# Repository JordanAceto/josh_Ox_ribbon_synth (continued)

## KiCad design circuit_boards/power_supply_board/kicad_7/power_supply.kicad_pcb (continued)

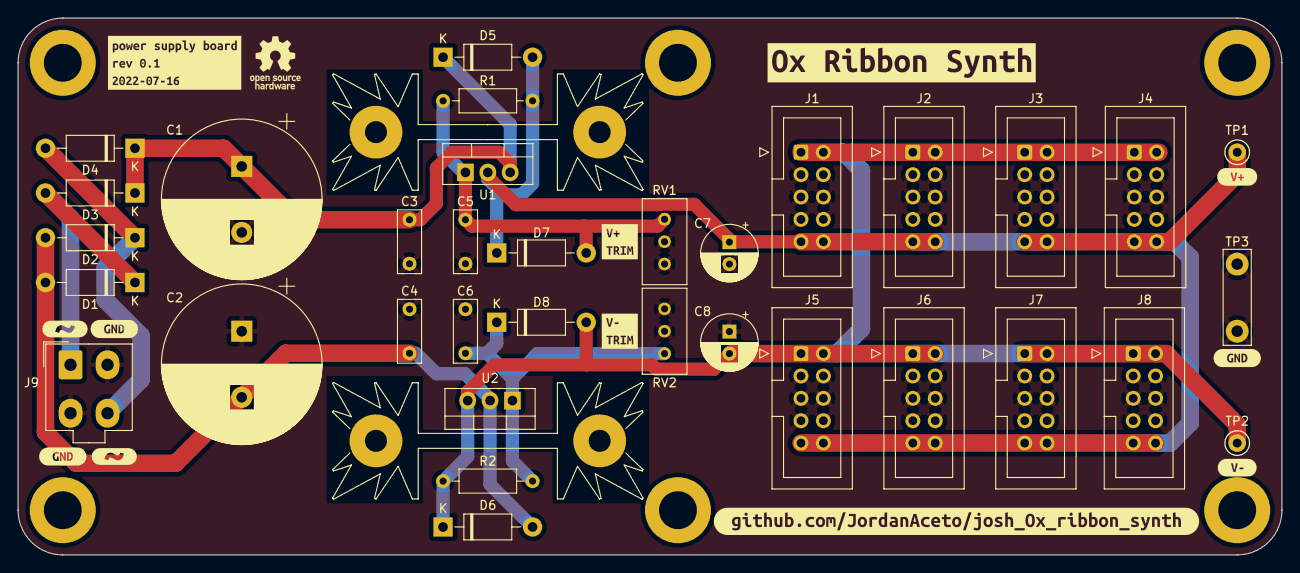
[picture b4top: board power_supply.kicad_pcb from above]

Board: 2 copper layers, 143.5 x 61.0 mm, 46 parts (0 on the bottom side), 9 nets.

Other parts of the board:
kibuzzard-62AC7A9F: G***; kibuzzard-62AC7A9F
kibuzzard-62B8A02A, kibuzzard-62B8A02A#2: G***; kibuzzard-62B8A02A
kibuzzard-62B8A297: G***; kibuzzard-62B8A297
kibuzzard-62B89F9F: G***; kibuzzard-62B89F9F
kibuzzard-62B89F93, kibuzzard-62B89F93#2, kibuzzard-62B89F93#3: G***; kibuzzard-62B89F93
kibuzzard-62B89FA9: G***; kibuzzard-62B89FA9
kibuzzard-62B89FC4: G***; kibuzzard-62B89FC4
kibuzzard-62B89FD2: G***; kibuzzard-62B89FD2
kibuzzard-62D2BBF1: G***; kibuzzard-62D2BBF1

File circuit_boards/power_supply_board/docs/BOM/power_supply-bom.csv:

Row,Description,Part,References,Value,Footprint,Quantity Per PCB,Status,Datasheet
1,Unpolarized capacitor,C,C3 C4 C5 C6,100n,C_Rect_L7.0mm_W2.5mm_P5.00mm,4, ,~
2,Polarized capacitor,C_Polarized,C7 C8,10u,CP_Radial_D6.3mm_P2.50mm,2, ,~
3,Polarized capacitor,C_Polarized,C1 C2,3300u,CP_Radial_D18.0mm_P7.50mm,2, ,~
4,"100V 1A General Purpose Rectifier Diode, DO-41",1N4002,D1 D2 D3 D4 D5 D6 D7 D8,1N4002,D_DO-41_SOD81_P10.16mm_Horizontal,8, ,http://www.vishay.com/docs/88503/1n4001.pdf
5,"Generic connector, single row, 01x04, script generated (kicad-library-utils/schlib/autogen/connector/)",Conn_01x04,J9,AC_power_in,Molex_Mini-Fit_Jr_5566-04A_2x02_P4.20mm_Vertical,1, ,~
6,"Generic connector, double row, 02x05, odd/even pin numbering scheme (row 1 odd numbers, row 2 even numbers), script generated (kicad-library-utils/schlib/autogen/connector/)",Conn_02x05_Odd_Even,J1 J2 J3 J4 J5 J6 J7 J8,power_out,IDC-Header_2x05_P2.54mm_Vertical,8, ,~
7,Resistor,R,R1 R2,240,R_Axial_DIN0207_L6.3mm_D2.5mm_P10.16mm_Horizontal,2, ,~
8,Trim-potentiometer,R_Potentiometer_Trim,RV1 RV2,5k,Potentiometer_Bourns_3296W_Vertical,2, ,~
9,"1.5A 35V Adjustable Linear Regulator, TO-220",LM317_TO-220,U1,LM317_TO-220,TO-220-3_Vertical,1, ,http://www.ti.com/lit/ds/symlink/lm317.pdf
10,"Negative 1.5A 35V Adjustable Linear Regulator, TO-220",LM337_TO220,U2,LM337_TO220,TO-220-3_Vertical,1, ,http://www.ti.com/lit/ds/symlink/lm337-n.pdf





Project info:
Schematic:,power_supply
Variant:,default
Revision:,0
Date:,2022-06-26
KiCad Version:,6.0.5+dfsg-1~bpo11+1
Statistics:
Component Groups:,10
Component Count:,31 (0 SMD/ 31 THT)
Fitted Components:,31 (0 SMD/ 31 THT)
Number of PCBs:,1
Total Components:,31

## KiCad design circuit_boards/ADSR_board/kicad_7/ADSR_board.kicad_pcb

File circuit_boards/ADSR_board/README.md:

# Triple ADSR Board

## [SCHEMATIC](https://github.com/JordanAceto/josh_Ox_ribbon_synth/blob/master/circuit_boards/ADSR_board/docs/ADSR_board_schematic.pdf)

Three ADSR envelope generators with short and long time range switch.

A comparator and analog switch ensure that the sustain control reacts quickly during sustain phases, even when the decay control is set for long time constants.

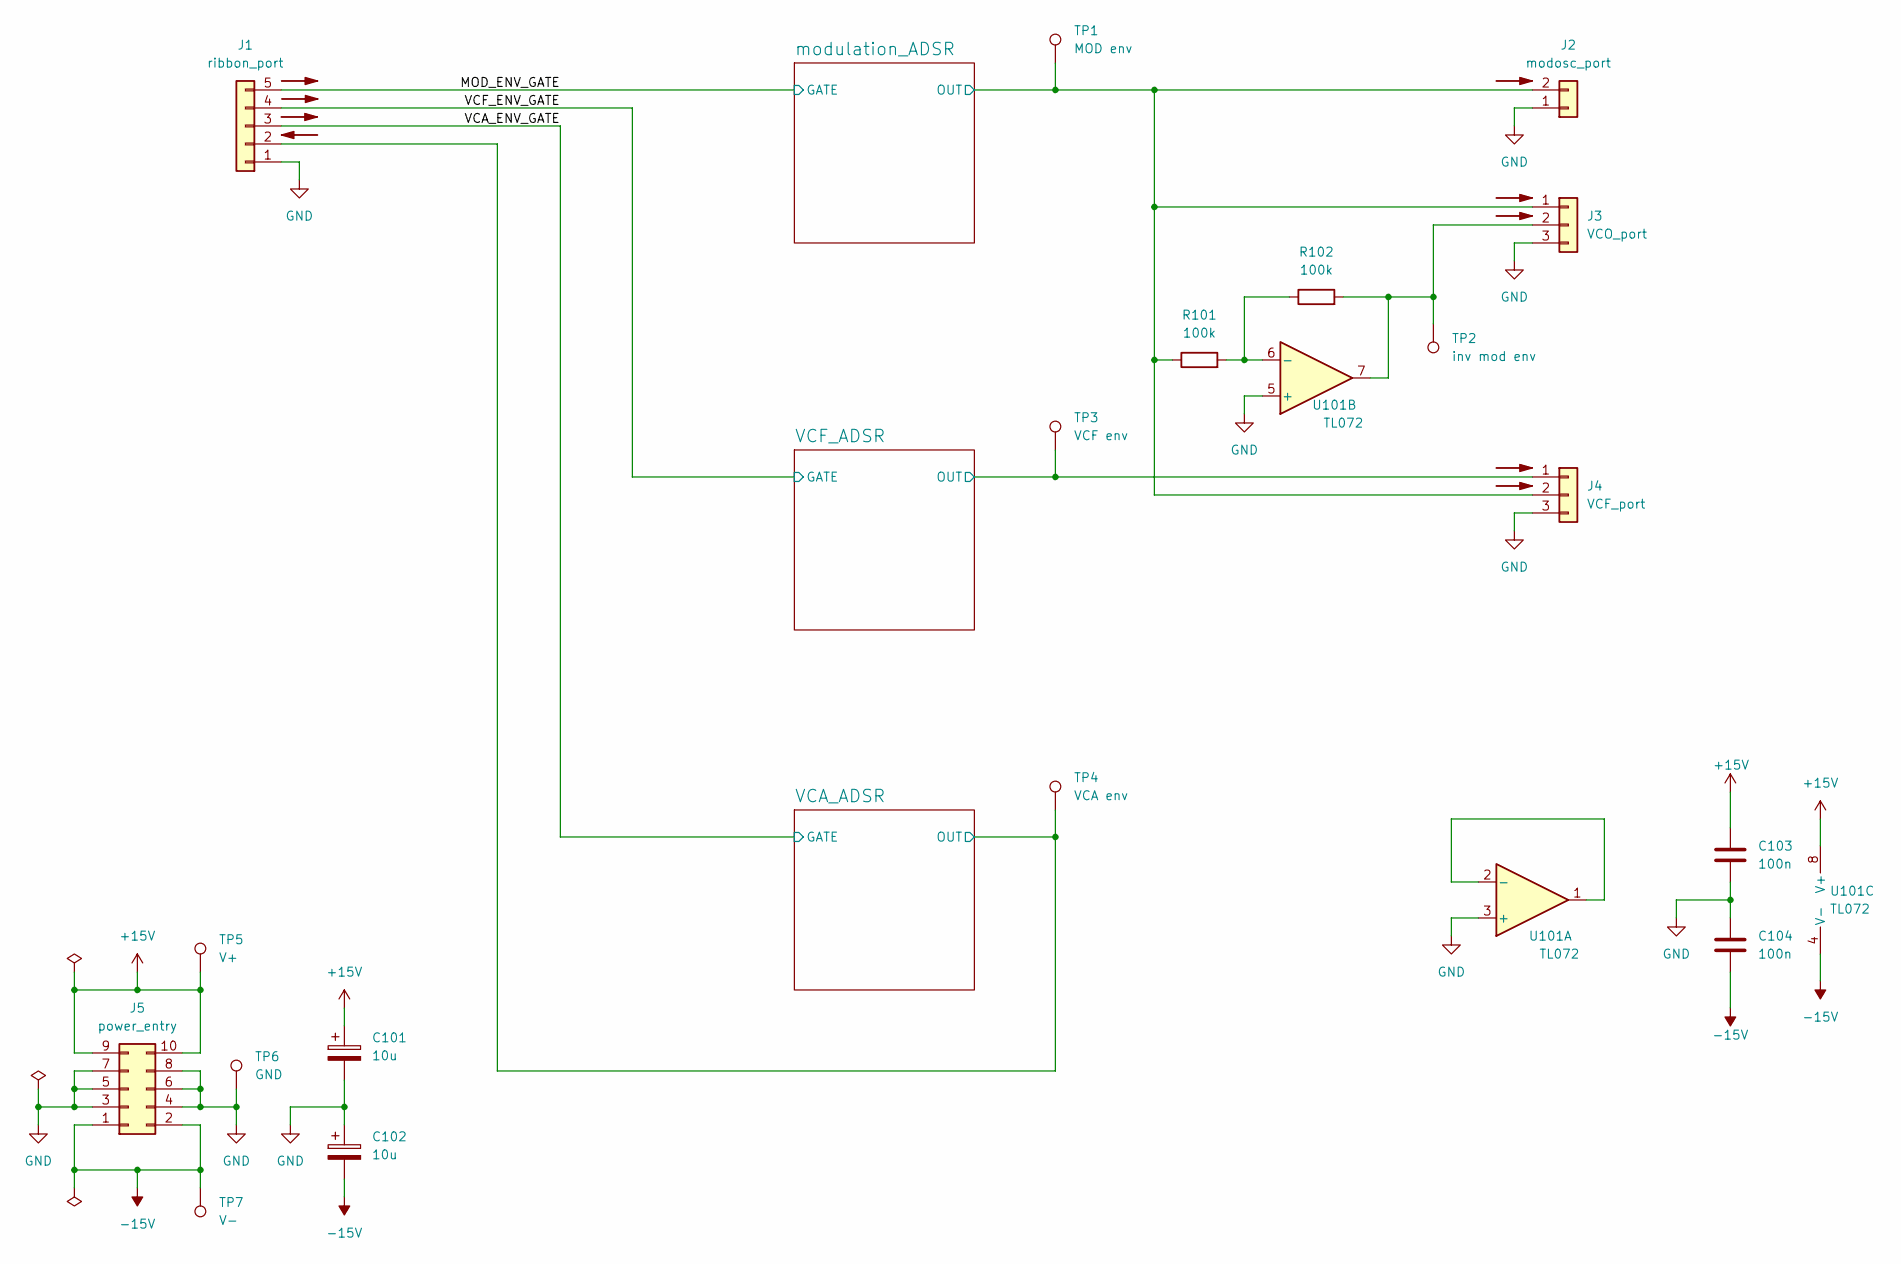
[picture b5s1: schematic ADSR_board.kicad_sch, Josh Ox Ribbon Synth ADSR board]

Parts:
C101, C102: 10u; CP_Radial_D6.3mm_P2.50mm
C103, C104: 100n; C_0805_2012Metric
J1: ribbon_port; Molex_KK-254_AE-6410-05A_1x05_P2.54mm_Vertical
J2: modosc_port; Molex_KK-254_AE-6410-02A_1x02_P2.54mm_Vertical
J3: VCO_port; Molex_KK-254_AE-6410-03A_1x03_P2.54mm_Vertical
J4: VCF_port; Molex_KK-254_AE-6410-03A_1x03_P2.54mm_Vertical
J5: power_entry; IDC-Header_2x05_P2.54mm_Vertical
R101, R102: 100k; R_0805_2012Metric
TP1: MOD env; TestPoint_Keystone_5000-5004_Miniature
TP2: inv mod env; TestPoint_Keystone_5000-5004_Miniature
TP3: VCF env; TestPoint_Keystone_5000-5004_Miniature
TP4: VCA env; TestPoint_Keystone_5000-5004_Miniature
TP5: V+; TestPoint_Keystone_5000-5004_Miniature
TP6: GND; TestPoint_Bridge_Pitch7.62mm_Drill1.3mm
TP7: V-; TestPoint_Keystone_5000-5004_Miniature
U101: TL072; SOIC-8_3.9x4.9mm_P1.27mm

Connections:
+15V: C101.1, C103.1, J5.9, J5.10, TP5.1, U101.8 (V+); also elsewhere on the board
-15V: C102.2, C104.2, J5.1, J5.2, TP7.1, U101.4 (V-); also elsewhere on the board
/MOD_ENV_GATE: J1.5; also elsewhere on the board
/VCA_ADSR/OUT: J1.2, TP4.1; also elsewhere on the board
/VCA_ENV_GATE: J1.3; also elsewhere on the board
/VCF_ADSR/OUT: J4.1, TP3.1; also elsewhere on the board
/VCF_ENV_GATE: J1.4; also elsewhere on the board
/modulation_ADSR/OUT: J2.2, J3.1, J4.2, R101.1, TP1.1; also elsewhere on the board
GND: C101.2, C102.1, C103.2, C104.1, J1.1, J2.1, J3.3, J4.3, J5.3, J5.4, J5.5, J5.6, J5.7, J5.8, TP6.1, U101.3 (+), U101.5 (+); also elsewhere on the board
unnamed: J3.2, R102.2, TP2.1, U101.7
unnamed: R101.2, R102.1, U101.6 (-)
unnamed: U101.1, U101.2 (-)

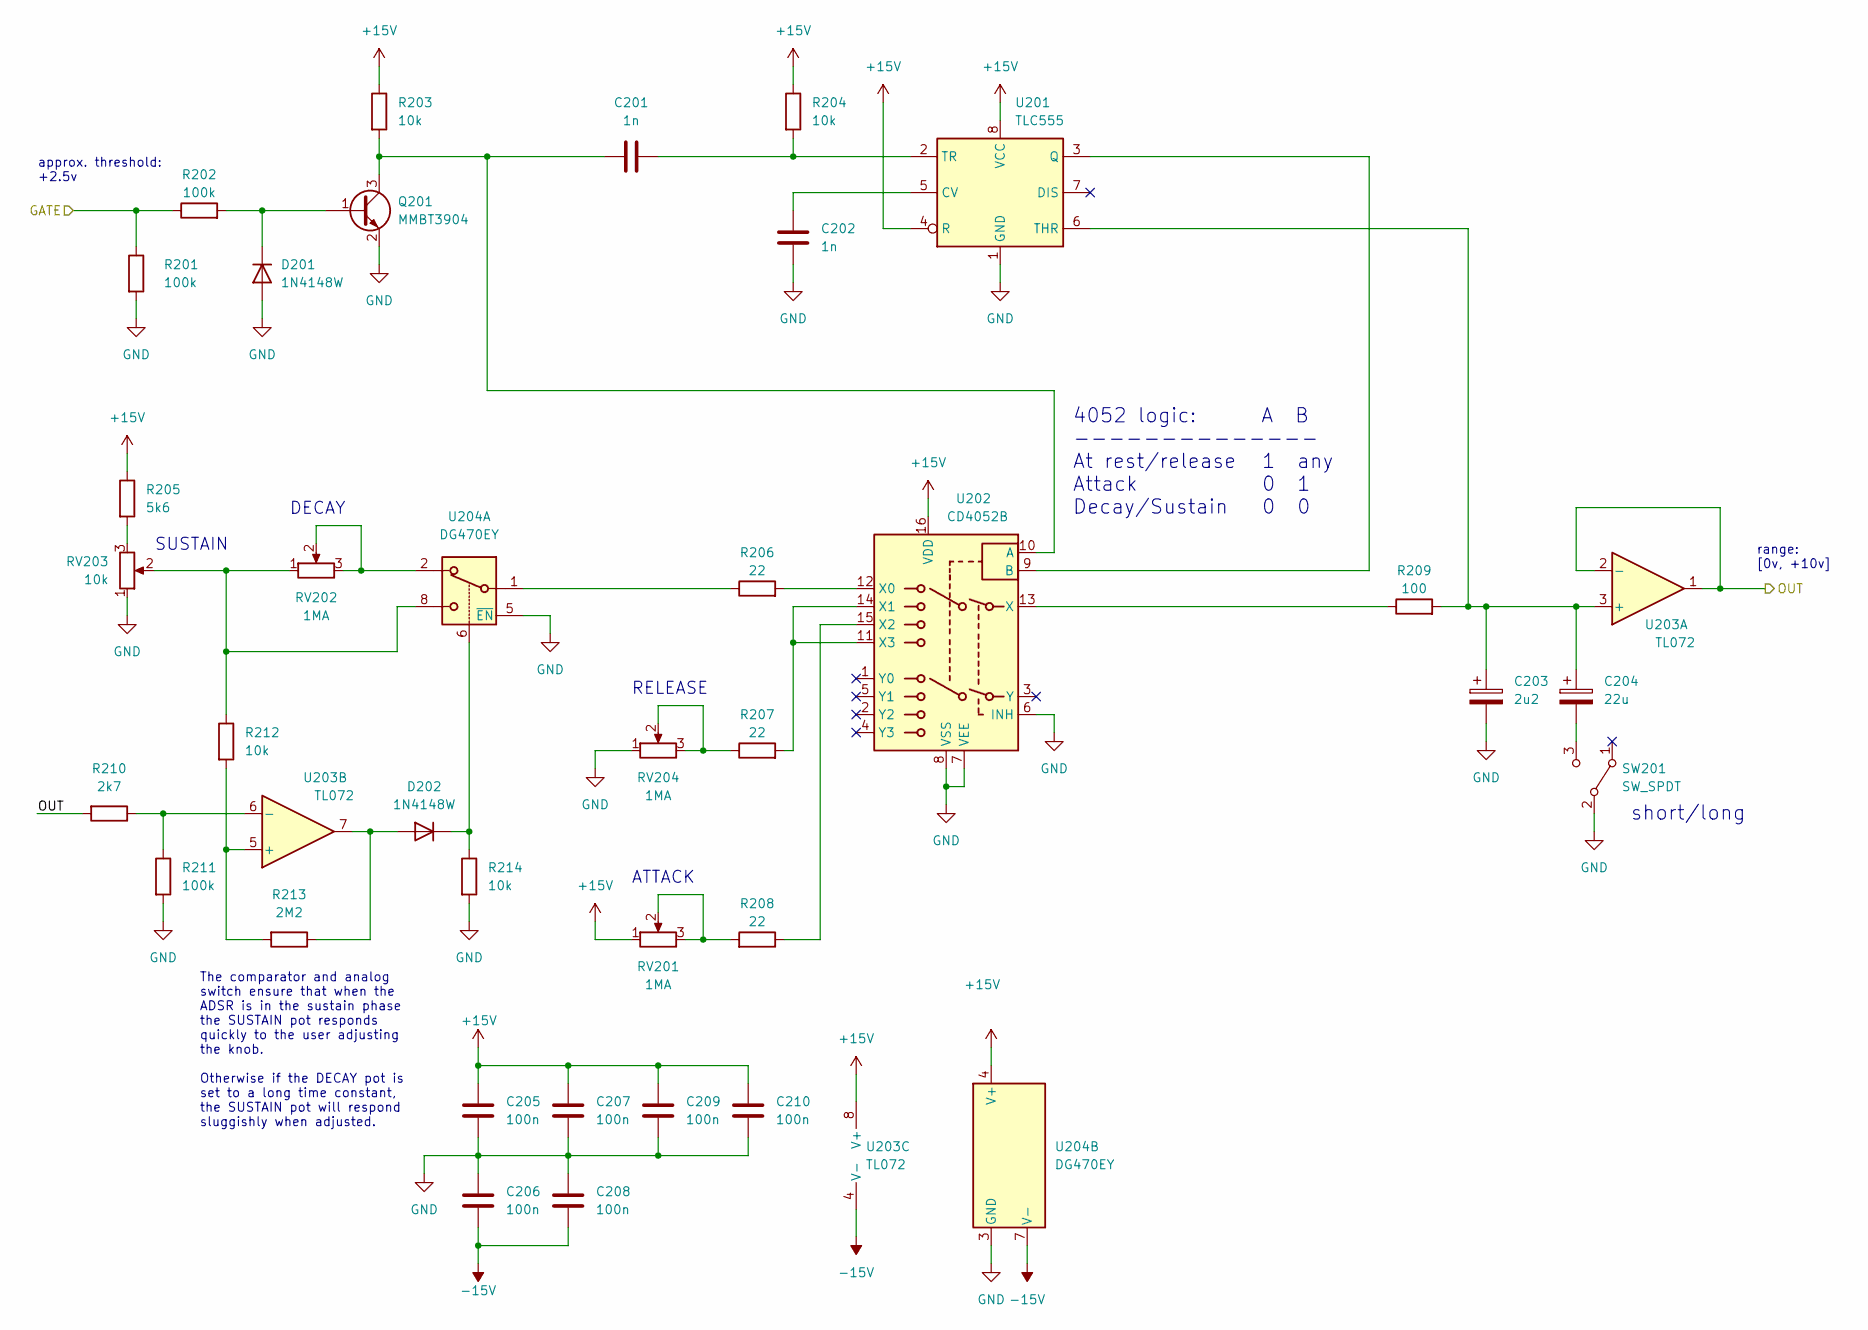
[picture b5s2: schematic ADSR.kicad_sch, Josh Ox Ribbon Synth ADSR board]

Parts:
C201, C202: 1n; C_0805_2012Metric
C203: 2u2; CP_Radial_D6.3mm_P2.50mm
C204: 22u; CP_Radial_D6.3mm_P2.50mm
C205, C206, C207, C208, C209, C210: 100n; C_0805_2012Metric
D201, D202: 1N4148W; D_SOD-123
Q201: MMBT3904; SOT-23
R201, R202, R211: 100k; R_0805_2012Metric
R203, R204, R212, R214: 10k; R_0805_2012Metric
R205: 5k6; R_0805_2012Metric
R206, R207, R208: 22; R_0805_2012Metric
R209: 100; R_0805_2012Metric
R210: 2k7; R_0805_2012Metric
R213: 2M2; R_0805_2012Metric
RV201, RV202, RV204: 1MA; Potentiometer_Alpha_RD901F-40-00D_Single_Vertical
RV203: 10k; Potentiometer_Alpha_RD901F-40-00D_Single_Vertical
SW201: SW_SPDT; SPDT_mini_toggle
U201: TLC555; SOIC-8_3.9x4.9mm_P1.27mm
U202: CD4052B; SOIC-16_3.9x9.9mm_P1.27mm
U203: TL072; SOIC-8_3.9x4.9mm_P1.27mm
U204: DG470EY; SOIC-8_3.9x4.9mm_P1.27mm

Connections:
+15V: C205.1, C207.1, C209.1, C210.1, R203.1, R204.1, R205.1, RV201.1, U201.4 (R), U201.8 (VCC), U202.16 (VDD), U203.8 (V+), U204.4 (V+); also elsewhere on the board
-15V: C206.2, C208.2, U203.4 (V-), U204.7 (V-); also elsewhere on the board
/MOD_ENV_GATE: R201.1, R202.1; also elsewhere on the board
/modulation_ADSR/OUT: R210.2, U203.1, U203.2 (-); also elsewhere on the board
GND: C202.2, C203.2, C205.2, C206.1, C207.2, C208.1, C209.2, C210.2, D201.2 (A), Q201.2 (E), R201.2, R211.2, R214.2, RV203.1, RV204.1, SW201.2 (B), U201.1 (GND), U202.6 (INH), U202.7 (VEE), U202.8 (VSS), U204.3 (GND), U204.5 (~EN); also elsewhere on the board
unnamed: C201.1, Q201.3 (C), R203.2, U202.10 (A)
unnamed: C201.2, R204.2, U201.2 (TR)
unnamed: C202.1, U201.5 (CV)
unnamed: C203.1, C204.1, R209.2, U201.6 (THR), U203.3 (+)
unnamed: C204.2, SW201.3 (C)
unnamed: D201.1 (K), Q201.1 (B), R202.2
unnamed: D202.1 (K), R214.1, U204.6
unnamed: D202.2 (A), R213.1, U203.7
unnamed: R205.2, RV203.3
unnamed: R206.1, U204.1
unnamed: R206.2, U202.12 (X0)
unnamed: R207.1, RV204.2, RV204.3
unnamed: R207.2, U202.11 (X3), U202.14 (X1)
unnamed: R208.1, U202.15 (X2)
unnamed: R208.2, RV201.2, RV201.3
unnamed: R209.1, U202.13 (X)
unnamed: R210.1, R211.1, U203.6 (-)
unnamed: R212.1, RV202.1, RV203.2, U204.8
unnamed: R212.2, R213.2, U203.5 (+)
unnamed: RV202.2, RV202.3, U204.2
unnamed: U201.3 (Q), U202.9 (B)

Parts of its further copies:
C301, C302, C401, C402: 1n; C_0805_2012Metric
C303, C403: 2u2; CP_Radial_D6.3mm_P2.50mm
C304, C404: 22u; CP_Radial_D6.3mm_P2.50mm
C305, C306, C307, C308, C309, C310, C405, C406, C407, C408, C409, C410: 100n; C_0805_2012Metric
D301, D302, D401, D402: 1N4148W; D_SOD-123
Q301, Q401: MMBT3904; SOT-23
R301, R302, R311, R401, R402, R411: 100k; R_0805_2012Metric
R303, R304, R312, R314, R403, R404, R412, R414: 10k; R_0805_2012Metric
R305, R405: 5k6; R_0805_2012Metric
R306, R307, R308, R406, R407, R408: 22; R_0805_2012Metric
R309, R409: 100; R_0805_2012Metric
R310, R410: 2k7; R_0805_2012Metric
R313, R413: 2M2; R_0805_2012Metric
RV301, RV302, RV304, RV401, RV402, RV404: 1MA; Potentiometer_Alpha_RD901F-40-00D_Single_Vertical
RV303, RV403: 10k; Potentiometer_Alpha_RD901F-40-00D_Single_Vertical
SW301, SW401: SW_SPDT; SPDT_mini_toggle
U301, U401: TLC555; SOIC-8_3.9x4.9mm_P1.27mm
U302, U402: CD4052B; SOIC-16_3.9x9.9mm_P1.27mm
U303, U403: TL072; SOIC-8_3.9x4.9mm_P1.27mm
U304, U404: DG470EY; SOIC-8_3.9x4.9mm_P1.27mm

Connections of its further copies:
+15V: C305.1, C307.1, C309.1, C310.1, C405.1, C407.1, C409.1, C410.1, R303.1, R304.1, R305.1, R403.1, R404.1, R405.1, RV301.1, RV401.1, U301.4 (R), U301.8 (VCC), U302.16 (VDD), U303.8 (V+), U304.4 (V+), U401.4 (R), U401.8 (VCC), U402.16 (VDD), U403.8 (V+), U404.4 (V+); also elsewhere on the board
-15V: C306.2, C308.2, C406.2, C408.2, U303.4 (V-), U304.7 (V-), U403.4 (V-), U404.7 (V-); also elsewhere on the board
/VCA_ADSR/OUT: R410.2, U403.1, U403.2 (-); also elsewhere on the board
/VCA_ENV_GATE: R401.1, R402.1; also elsewhere on the board
/VCF_ADSR/OUT: R310.2, U303.1, U303.2 (-); also elsewhere on the board
/VCF_ENV_GATE: R301.1, R302.1; also elsewhere on the board
GND: C302.2, C303.2, C305.2, C306.1, C307.2, C308.1, C309.2, C310.2, C402.2, C403.2, C405.2, C406.1, C407.2, C408.1, C409.2, C410.2, D301.2 (A), D401.2 (A), Q301.2 (E), Q401.2 (E), R301.2, R311.2, R314.2, R401.2, R411.2, R414.2, RV303.1, RV304.1, RV403.1, RV404.1, SW301.2 (B), SW401.2 (B), U301.1 (GND), U302.6 (INH), U302.7 (VEE), U302.8 (VSS), U304.3 (GND), U304.5 (~EN), U401.1 (GND), U402.6 (INH), U402.7 (VEE), U402.8 (VSS), U404.3 (GND), U404.5 (~EN); also elsewhere on the board
unnamed: C301.1, Q301.3 (C), R303.2, U302.10 (A)
unnamed: C301.2, R304.2, U301.2 (TR)
unnamed: C302.1, U301.5 (CV)
unnamed: C303.1, C304.1, R309.2, U301.6 (THR), U303.3 (+)
unnamed: C304.2, SW301.3 (C)
unnamed: C401.1, Q401.3 (C), R403.2, U402.10 (A)
unnamed: C401.2, R404.2, U401.2 (TR)
unnamed: C402.1, U401.5 (CV)
unnamed: C403.1, C404.1, R409.2, U401.6 (THR), U403.3 (+)
unnamed: C404.2, SW401.3 (C)
unnamed: D301.1 (K), Q301.1 (B), R302.2
unnamed: D302.1 (K), R314.1, U304.6
unnamed: D302.2 (A), R313.1, U303.7
unnamed: D401.1 (K), Q401.1 (B), R402.2
unnamed: D402.1 (K), R414.1, U404.6
unnamed: D402.2 (A), R413.1, U403.7
unnamed: R305.2, RV303.3
unnamed: R306.1, U304.1
unnamed: R306.2, U302.12 (X0)
unnamed: R307.1, RV304.2, RV304.3
unnamed: R307.2, U302.11 (X3), U302.14 (X1)
unnamed: R308.1, U302.15 (X2)
unnamed: R308.2, RV301.2, RV301.3
unnamed: R309.1, U302.13 (X)
unnamed: R310.1, R311.1, U303.6 (-)
unnamed: R312.1, RV302.1, RV303.2, U304.8
unnamed: R312.2, R313.2, U303.5 (+)
unnamed: R405.2, RV403.3
unnamed: R406.1, U404.1
unnamed: R406.2, U402.12 (X0)
unnamed: R407.1, RV404.2, RV404.3
unnamed: R407.2, U402.11 (X3), U402.14 (X1)
unnamed: R408.1, U402.15 (X2)
unnamed: R408.2, RV401.2, RV401.3
unnamed: R409.1, U402.13 (X)
unnamed: R410.1, R411.1, U403.6 (-)
unnamed: R412.1, RV402.1, RV403.2, U404.8
unnamed: R412.2, R413.2, U403.5 (+)
unnamed: RV302.2, RV302.3, U304.2
unnamed: RV402.2, RV402.3, U404.2
unnamed: U301.3 (Q), U302.9 (B)
unnamed: U401.3 (Q), U402.9 (B)

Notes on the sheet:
range: [0v, +10v]
DECAY
RELEASE
SUSTAIN
ATTACK
short/long
The comparator and analog switch ensure that when the ADSR is in the sustain phase the SUSTAIN pot responds quickly to the user adjusting the knob. Otherwise if the DECAY pot is set to a long time constant, the SUSTAIN pot will respond sluggishly when adjusted.
approx. threshold: +2.5v
1 any 0 1 0 0
4052 logic: A B -------------- At rest/release Attack Decay/Sustain

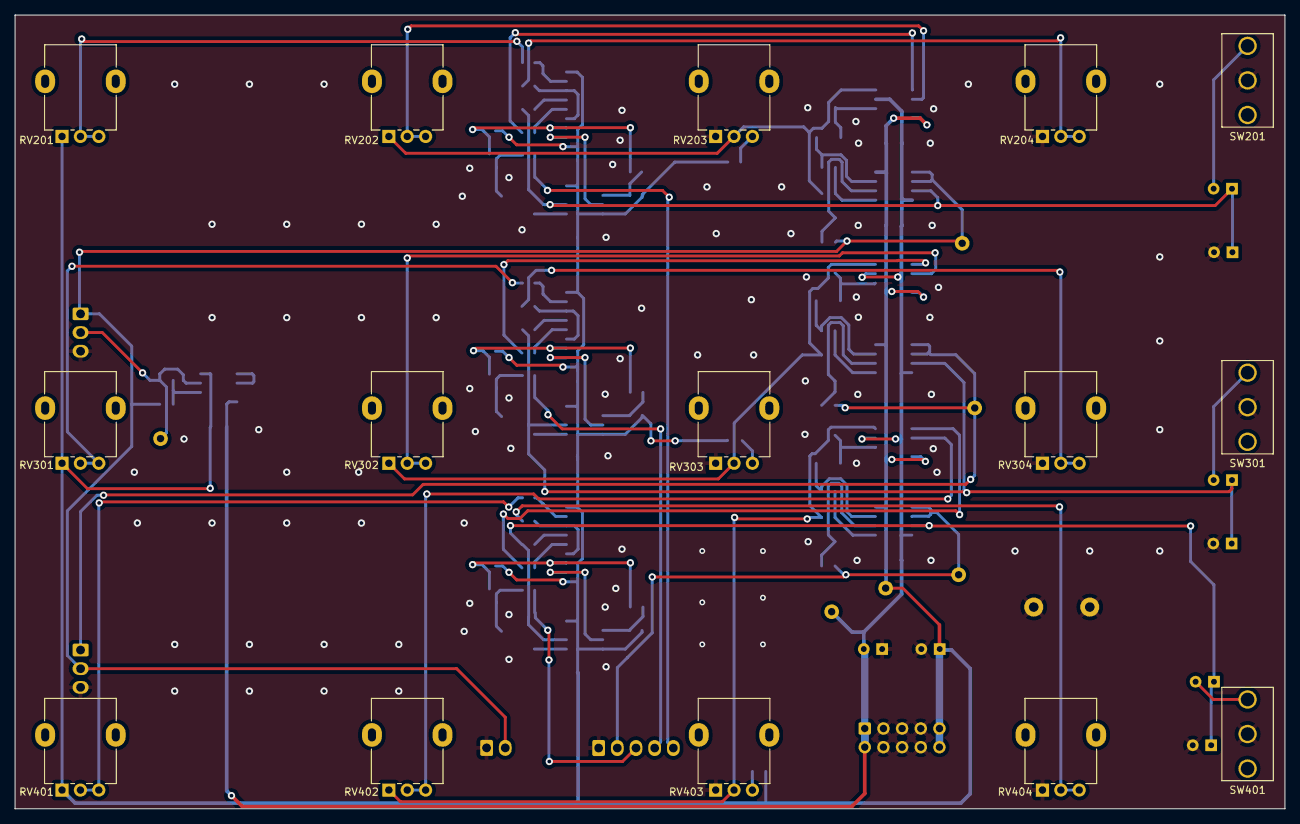
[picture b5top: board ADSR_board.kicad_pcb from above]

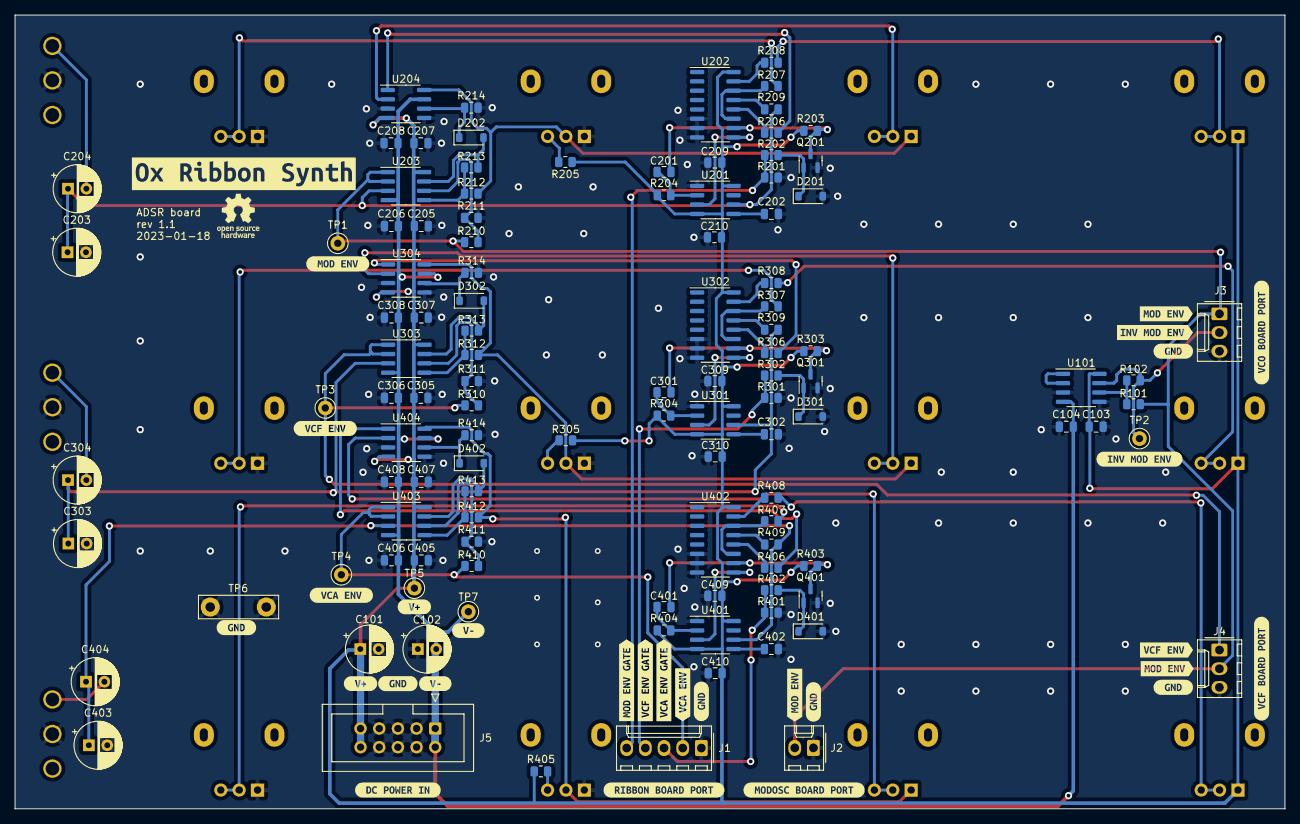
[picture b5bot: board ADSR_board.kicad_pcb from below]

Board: 2 copper layers, 172.7 x 107.9 mm, 156 parts (141 on the bottom side), 75 nets.

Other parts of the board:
kibuzzard-62AC7A9F: G***; kibuzzard-62AC7A9F
kibuzzard-62AC77C9: G***; kibuzzard-62AC77C9
kibuzzard-62AC77E4: G***; kibuzzard-62AC77E4
kibuzzard-62AC77FB: G***; kibuzzard-62AC77FB
kibuzzard-62AC78CB: G***; kibuzzard-62AC78CB
kibuzzard-62AC79A3: G***; kibuzzard-62AC79A3
kibuzzard-62AC79C5: G***; kibuzzard-62AC79C5
kibuzzard-62AC755C, kibuzzard-62AC755C#2, kibuzzard-62AC755C#3, kibuzzard-62AC755C#4, kibuzzard-62AC755C#5, kibuzzard-62AC755C#6: G***; kibuzzard-62AC755C
kibuzzard-62AC758B, kibuzzard-62AC758B#2: G***; kibuzzard-62AC758B
kibuzzard-62AC762D: G***; kibuzzard-62AC762D
kibuzzard-62AC769B: G***; kibuzzard-62AC769B
kibuzzard-62AC791A, kibuzzard-62AC791A#2: G***; kibuzzard-62AC791A
kibuzzard-62AC792A, kibuzzard-62AC792A#2: G***; kibuzzard-62AC792A
kibuzzard-62AC7596: G***; kibuzzard-62AC7596
kibuzzard-62AC7711: G***; kibuzzard-62AC7711
kibuzzard-62AC7737: G***; kibuzzard-62AC7737
kibuzzard-62AC7758: G***; kibuzzard-62AC7758
kibuzzard-62AC7771: G***; kibuzzard-62AC7771
kibuzzard-62AC7810: G***; kibuzzard-62AC7810
kibuzzard-62AC7972: G***; kibuzzard-62AC7972
kibuzzard-62AC7989: G***; kibuzzard-62AC7989

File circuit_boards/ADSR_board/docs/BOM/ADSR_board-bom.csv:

Row,Description,Part,References,Value,Footprint,Quantity Per PCB,Status,Datasheet
1,Unpolarized capacitor,C,C201 C202 C301 C302 C401 C402,1n,C_0805_2012Metric,6, ,~
2,Unpolarized capacitor,C,C103 C104 C205 C206 C207 C208 C209 C210 C305 C306 C307 C308 C309 C310 C405 C406 C407 C408 C409 C410,100n,C_0805_2012Metric,20, ,~
3,Polarized capacitor,C_Polarized,C203 C303 C403,2u2,CP_Radial_D6.3mm_P2.50mm,3, ,~
4,Polarized capacitor,C_Polarized,C101 C102,10u,CP_Radial_D6.3mm_P2.50mm,2, ,~
5,Polarized capacitor,C_Polarized,C204 C304 C404,22u,CP_Radial_D6.3mm_P2.50mm,3, ,~
6,"75V 0.15A Fast Switching Diode, SOD-123",1N4148W,D201 D202 D301 D302 D401 D402,1N4148W,D_SOD-123,6, ,https://www.vishay.com/docs/85748/1n4148w.pdf
7,"Generic connector, single row, 01x03, script generated (kicad-library-utils/schlib/autogen/connector/)",Conn_01x03,J3 J4,VCO_port,Molex_KK-254_AE-6410-03A_1x03_P2.54mm_Vertical,2, ,~
8,"Generic connector, single row, 01x02, script generated (kicad-library-utils/schlib/autogen/connector/)",Conn_01x02,J2,modosc_port,Molex_KK-254_AE-6410-02A_1x02_P2.54mm_Vertical,1, ,~
9,"Generic connector, double row, 02x05, odd/even pin numbering scheme (row 1 odd numbers, row 2 even numbers), script generated (kicad-library-utils/schlib/autogen/connector/)",Conn_02x05_Odd_Even,J5,power_entry,IDC-Header_2x05_P2.54mm_Vertical,1, ,~
10,"Generic connector, single row, 01x05, script generated (kicad-library-utils/schlib/autogen/connector/)",Conn_01x05,J1,ribbon_port,Molex_KK-254_AE-6410-05A_1x05_P2.54mm_Vertical,1, ,~
11,"0.2A Ic, 40V Vce, Small Signal NPN Transistor, SOT-23",MMBT3904,Q201 Q301 Q401,MMBT3904,SOT-23,3, ,https://www.onsemi.com/pub/Collateral/2N3903-D.PDF
12,Resistor,R,R206 R207 R208 R306 R307 R308 R406 R407 R408,22,R_0805_2012Metric,9, ,~
13,Resistor,R,R209 R309 R409,100,R_0805_2012Metric,3, ,~
14,Resistor,R,R210 R310 R410,2k7,R_0805_2012Metric,3, ,~
15,Resistor,R,R205 R305 R405,5k6,R_0805_2012Metric,3, ,~
16,Resistor,R,R203 R204 R212 R214 R303 R304 R312 R314 R403 R404 R412 R414,10k,R_0805_2012Metric,12, ,~
17,Resistor,R,R101 R102 R201 R202 R211 R301 R302 R311 R401 R402 R411,100k,R_0805_2012Metric,11, ,~
18,Resistor,R,R213 R313 R413,2M2,R_0805_2012Metric,3, ,~
19,Potentiometer,R_Potentiometer,RV203 RV303 RV403,10k,Potentiometer_Alpha_RD901F-40-00D_Single_Vertical,3, ,~
20,Potentiometer,R_Potentiometer,RV201 RV202 RV204 RV301 RV302 RV304 RV401 RV402 RV404,1MA,Potentiometer_Alpha_RD901F-40-00D_Single_Vertical,9, ,~
21,"Switch, single pole double throw",SW_SPDT,SW201 SW301 SW401,SW_SPDT,SPDT_mini_toggle,3, ,~
22,"CMOS double 4-channel analog multiplexer/demultiplexer, TSSOP-16/DIP-16/SOIC-16",CD4052B,U202 U302 U402,CD4052B,SOIC-16_3.9x9.9mm_P1.27mm,3, ,http://www.ti.com/lit/ds/symlink/cd4052b.pdf
23,"Single SPDT 3V Logic Compatible CMOS Analog Switch, 35Ohm Ron, with Vlogic, DIP-8",DG470EY,U204 U304 U404,DG470EY,SOIC-8_3.9x4.9mm_P1.27mm,3, ,https://www.vishay.com/docs/71470/dg469.pdf
24,"Dual Low-Noise JFET-Input Operational Amplifiers, DIP-8/SOIC-8",TL072,U101 U203 U303 U403,TL072,SOIC-8_3.9x4.9mm_P1.27mm,4, ,http://www.ti.com/lit/ds/symlink/tl071.pdf
25,"Single LinCMOS Timer, 555 compatible, SOIC-8",TLC555xD,U201 U301 U401,TLC555,SOIC-8_3.9x4.9mm_P1.27mm,3, ,http://www.ti.com/lit/ds/symlink/tlc555.pdf





Project info:
Schematic:,ADSR_board
Variant:,default
Revision:,1.1
Date:,2023-01-18
KiCad Version:,6.0.5+dfsg-1~bpo11+1
Statistics:
Component Groups:,25
Component Count:,120 (85 SMD/ 28 THT)
Fitted Components:,120 (85 SMD/ 28 THT)
Number of PCBs:,1
Total Components:,120

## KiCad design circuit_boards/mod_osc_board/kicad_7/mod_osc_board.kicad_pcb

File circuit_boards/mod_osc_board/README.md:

# Modulation Oscillator

## [SCHEMATIC](https://github.com/JordanAceto/josh_Ox_ribbon_synth/blob/master/circuit_boards/mod_osc_board/docs/mod_osc_board_schematic.pdf)

Auxilliary modulation oscillator
- SSI21340 VCO core
- sine, triangle, up and down-going sawtooth, and square waveforms
- wide frequency range with three range settings (low, normal, high)
- tracks the ribbon controller

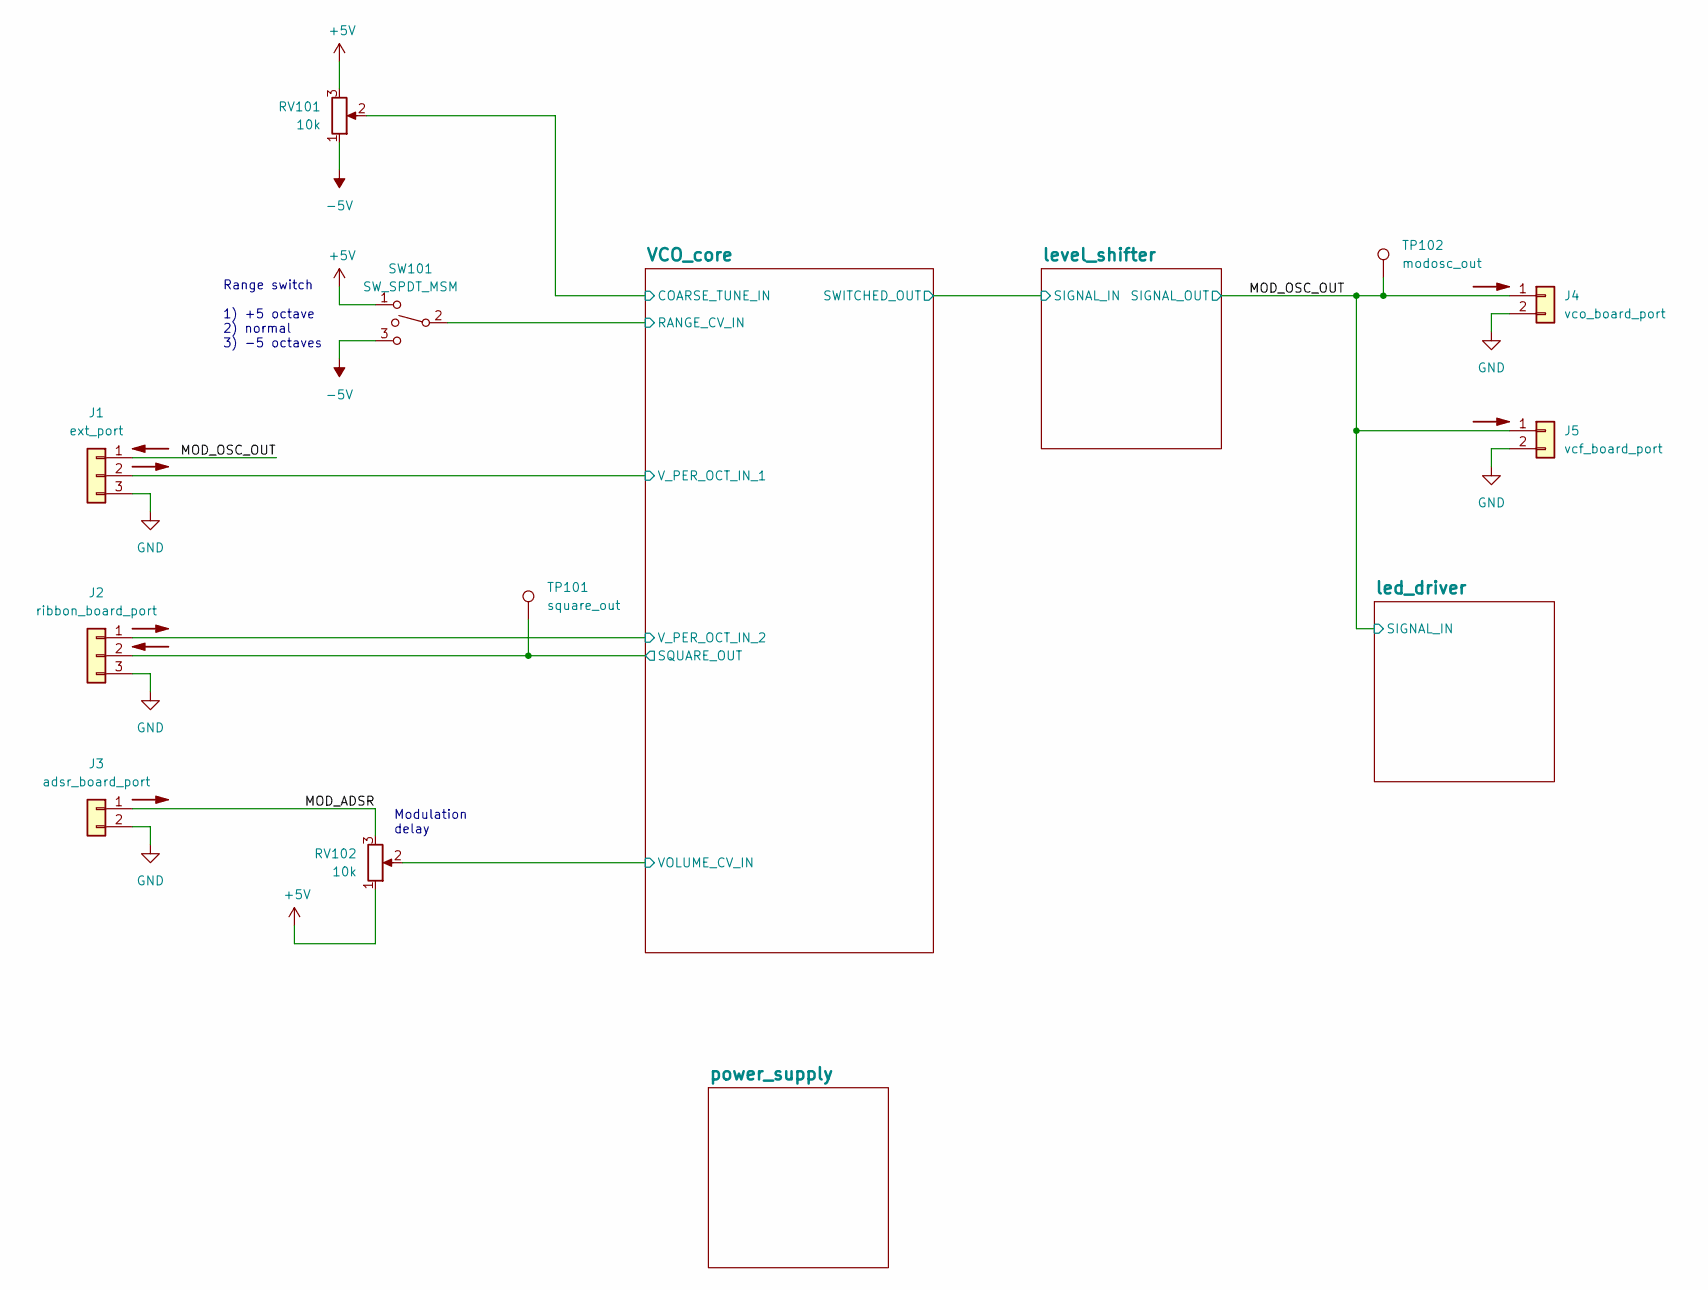
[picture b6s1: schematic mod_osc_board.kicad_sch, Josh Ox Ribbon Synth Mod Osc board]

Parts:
J1: ext_port; Molex_KK-254_AE-6410-03A_1x03_P2.54mm_Vertical
J2: ribbon_board_port; Molex_KK-254_AE-6410-03A_1x03_P2.54mm_Vertical
J3: adsr_board_port; Molex_KK-254_AE-6410-02A_1x02_P2.54mm_Vertical
J4: vco_board_port; Molex_KK-254_AE-6410-02A_1x02_P2.54mm_Vertical
J5: vcf_board_port; Molex_KK-254_AE-6410-02A_1x02_P2.54mm_Vertical
RV101, RV102: 10k; Potentiometer_P260T
SW101: SW_SPDT_MSM; SPDT_mini_toggle
TP101: square_out; TestPoint_Keystone_5000-5004_Miniature
TP102: modosc_out; TestPoint_Keystone_5000-5004_Miniature

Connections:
+5V: RV101.3, RV102.1, SW101.1; also elsewhere on the board
-5V: RV101.1, SW101.3; also elsewhere on the board
/MOD_ADSR: J3.1, RV102.3
/MOD_OSC_OUT: J1.1, J4.1, J5.1, TP102.1; also elsewhere on the board
/VCO_core/COARSE_TUNE_IN: RV101.2; also elsewhere on the board
/VCO_core/RANGE_CV_IN: SW101.2; also elsewhere on the board
/VCO_core/SQUARE_OUT: J2.2, TP101.1; also elsewhere on the board
/VCO_core/VOLUME_CV_IN: RV102.2; also elsewhere on the board
/VCO_core/V_PER_OCT_IN_1: J1.2; also elsewhere on the board
/VCO_core/V_PER_OCT_IN_2: J2.1; also elsewhere on the board

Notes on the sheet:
Range switch 1) +5 octave 2) normal 3) -5 octaves
Modulation delay
